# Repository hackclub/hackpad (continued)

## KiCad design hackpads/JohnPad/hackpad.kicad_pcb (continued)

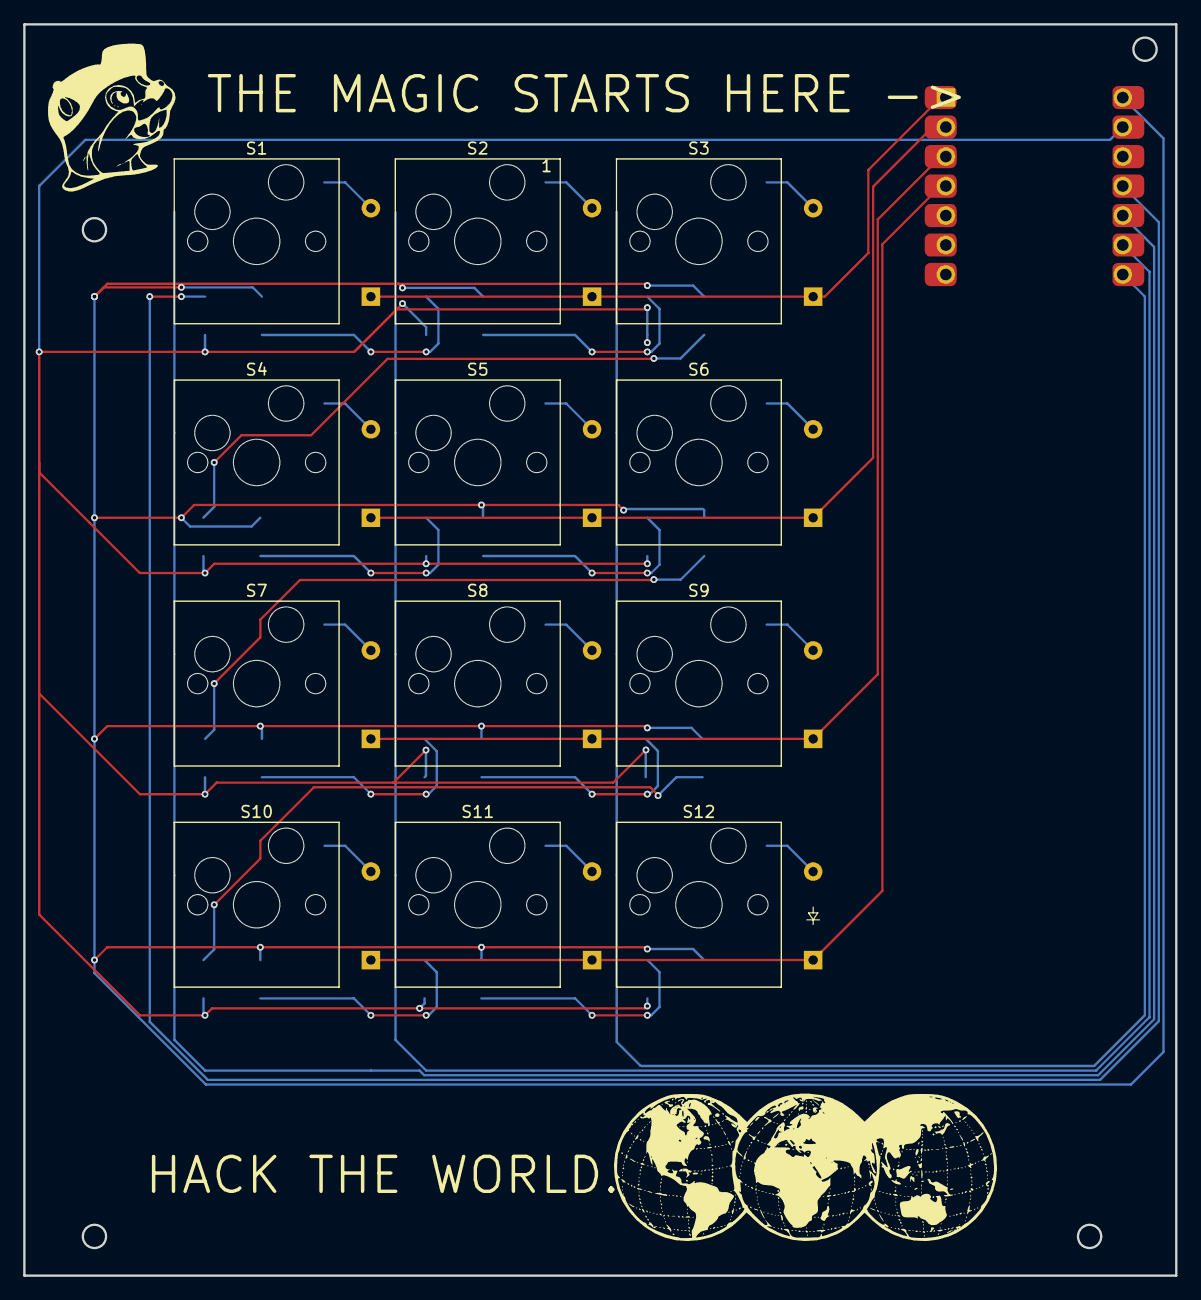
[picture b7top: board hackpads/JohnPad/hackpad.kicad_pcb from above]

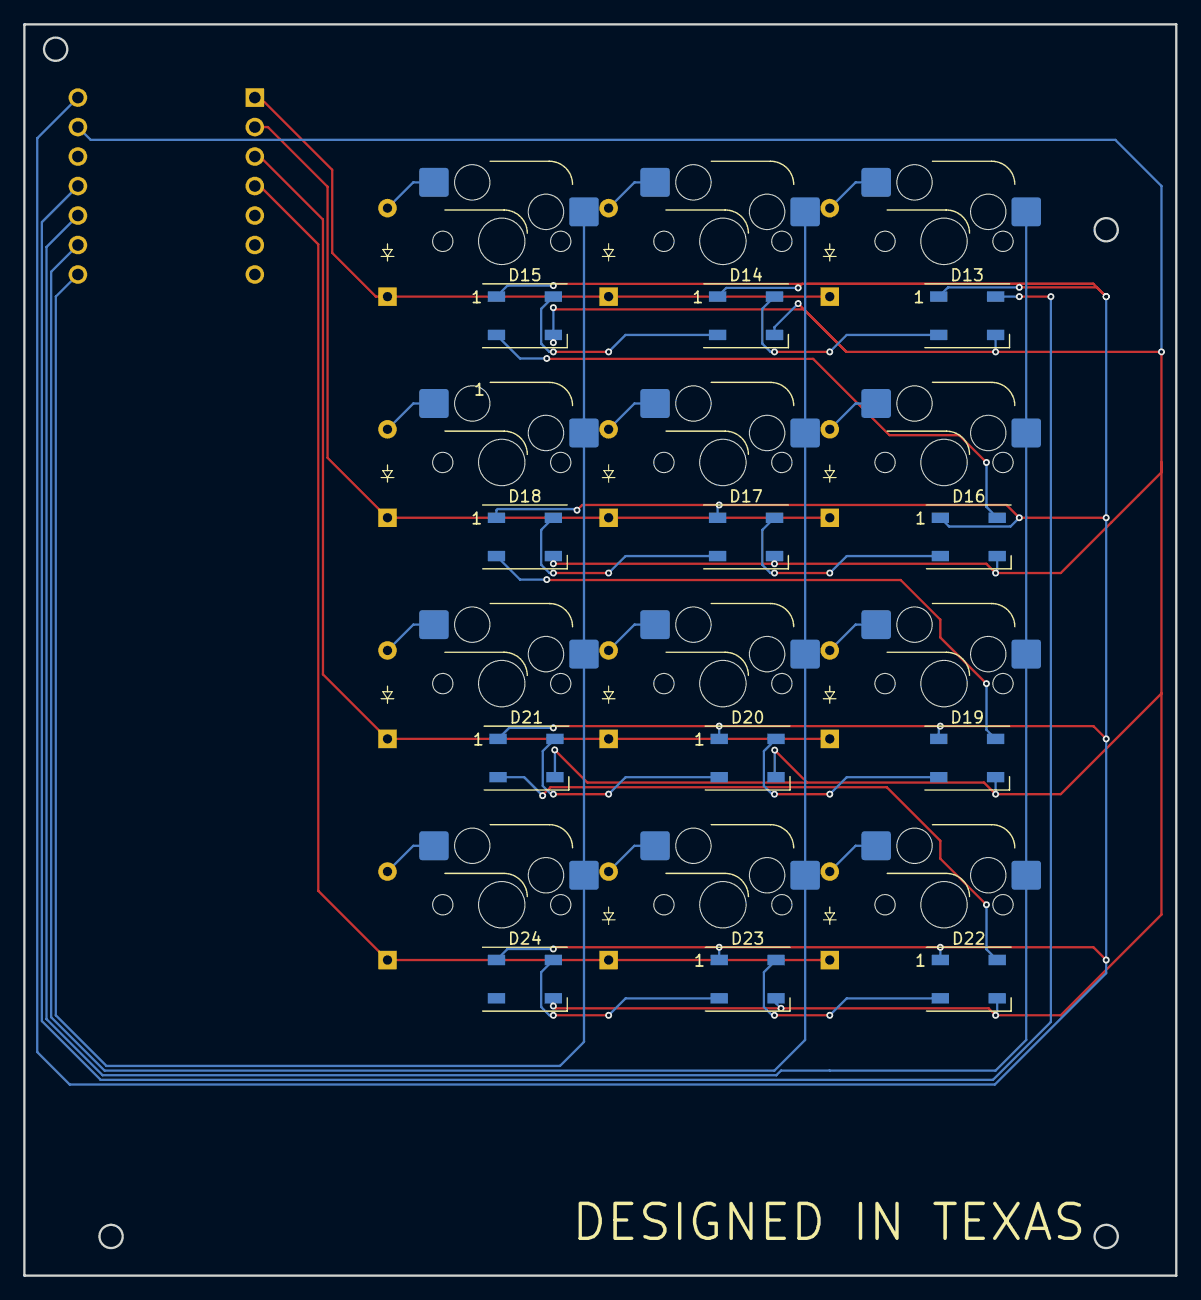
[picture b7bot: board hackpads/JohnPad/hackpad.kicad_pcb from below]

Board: 2 copper layers, 99.2 x 107.8 mm, 37 parts (23 on the bottom side), 33 nets.
